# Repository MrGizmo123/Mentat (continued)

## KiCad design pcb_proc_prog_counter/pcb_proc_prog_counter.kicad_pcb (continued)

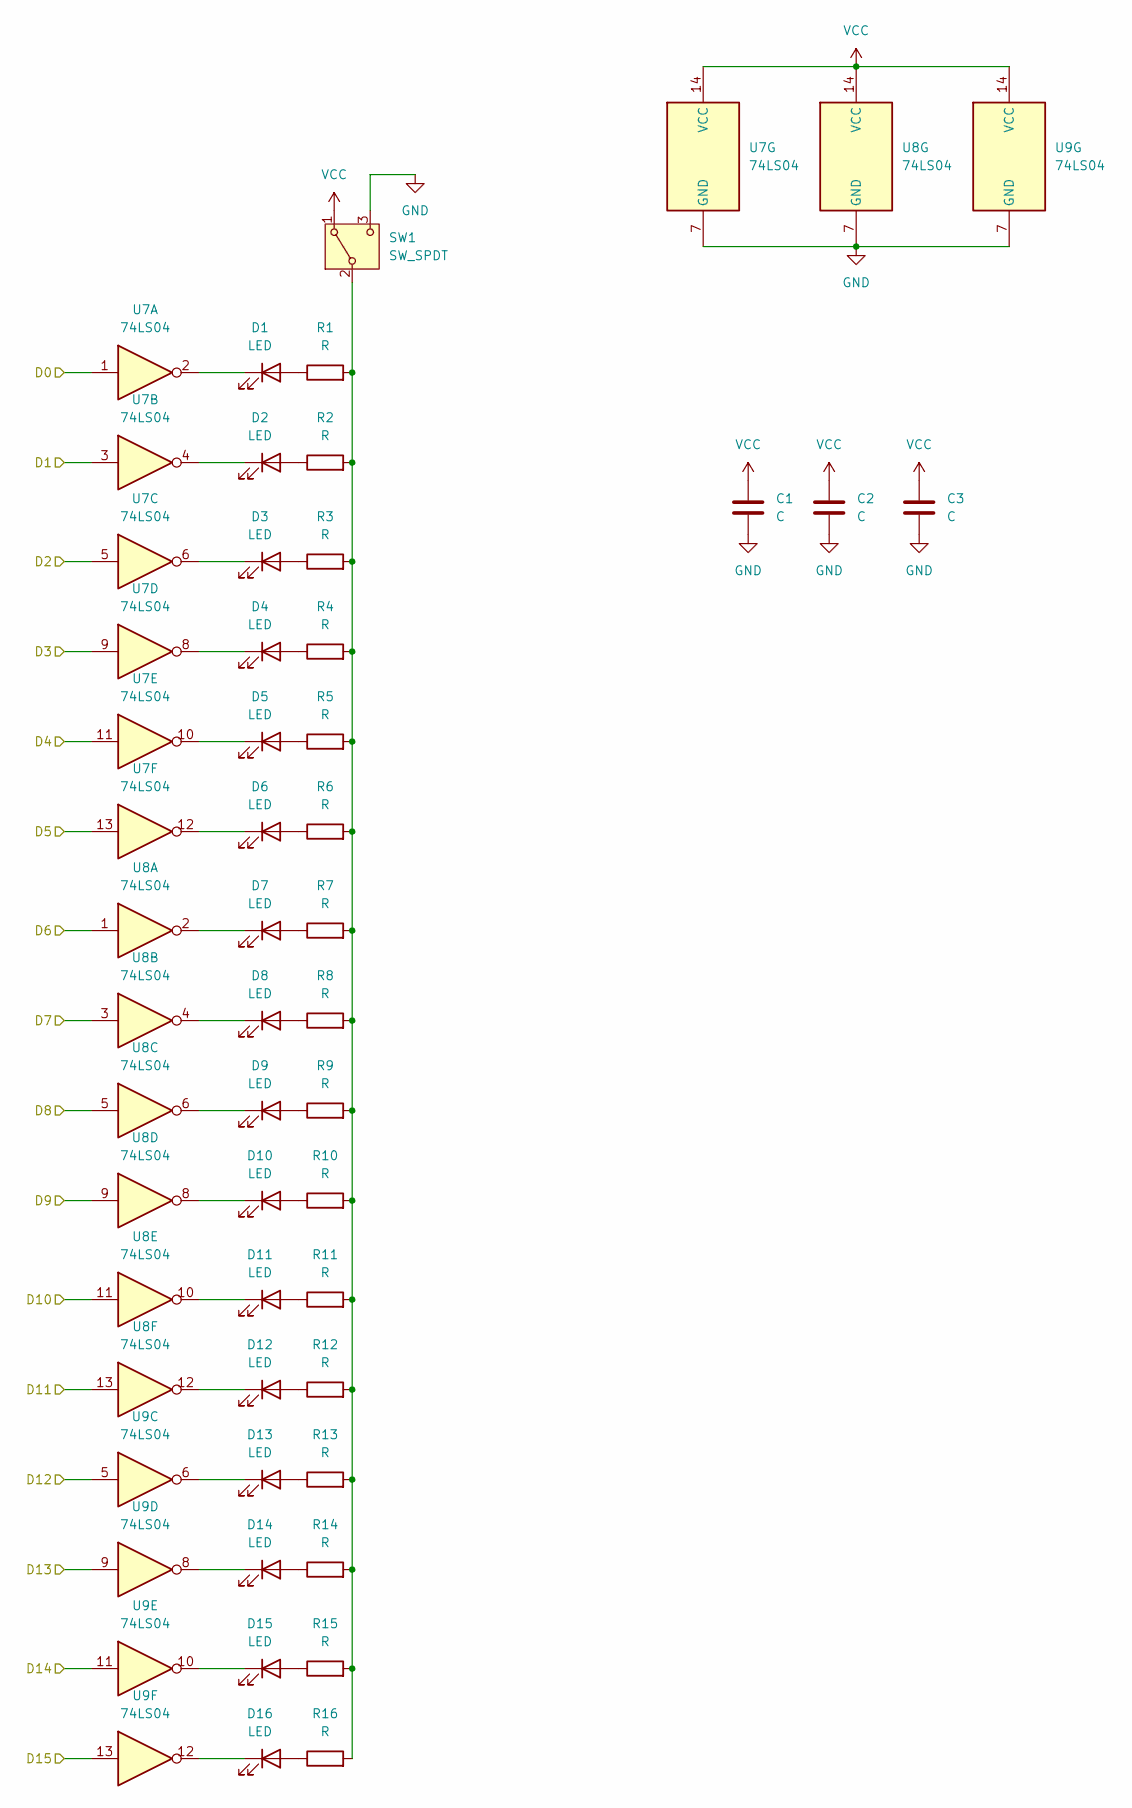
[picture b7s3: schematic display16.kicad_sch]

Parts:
C1, C2, C3: C; C_0805_2012Metric
D1, D2, D3, D4, D5, D6, D7, D8, D9, D10, D11, D12, D13, D14, D15, D16: LED; LED_Rectangular_W5.0mm_H2.0mm
R1, R2, R3, R4, R5, R6, R7, R8, R9, R10, R11, R12, R13, R14, R15, R16: R; R_0805_2012Metric
SW1: SW_SPDT; SW_E-Switch_EG1271_SPDT
U7: 74LS04; DIP-14_W7.62mm_Socket_LongPads
U8, U9: 74LS04; DIP-14_W7.62mm_LongPads

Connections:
/Display/D0: U7.1; also elsewhere on the board
/Display/D1: U7.3; also elsewhere on the board
/Display/D2: U7.5; also elsewhere on the board
/Display/D3: U7.9; also elsewhere on the board
/Display/D4: U7.11; also elsewhere on the board
/Display/D5: U7.13; also elsewhere on the board
/Display/D6: U8.1; also elsewhere on the board
/Display/D7: U8.3; also elsewhere on the board
/Display/D8: U8.5; also elsewhere on the board
/Display/D9: U8.9; also elsewhere on the board
/Display/D10: U8.11; also elsewhere on the board
/Display/D11: U8.13; also elsewhere on the board
/Display/D12: U9.5; also elsewhere on the board
/Display/D13: U9.9; also elsewhere on the board
/Display/D14: U9.11; also elsewhere on the board
/Display/D15: U9.13; also elsewhere on the board
GND: C1.2, C2.2, C3.2, SW1.3 (C), U7.7 (GND), U8.7 (GND), U9.7 (GND); also elsewhere on the board
unnamed: D1.2 (A), R1.1
unnamed: D1.1 (K), U7.2
unnamed: D2.2 (A), R2.1
unnamed: D2.1 (K), U7.4
unnamed: D3.2 (A), R3.1
unnamed: D3.1 (K), U7.6
unnamed: D4.2 (A), R4.1
unnamed: D4.1 (K), U7.8
unnamed: D5.2 (A), R5.1
unnamed: D5.1 (K), U7.10
unnamed: D6.2 (A), R6.1
unnamed: D6.1 (K), U7.12
unnamed: D7.2 (A), R7.1
unnamed: D7.1 (K), U8.2
unnamed: D8.2 (A), R8.1
unnamed: D8.1 (K), U8.4
unnamed: D9.2 (A), R9.1
unnamed: D9.1 (K), U8.6
unnamed: D10.2 (A), R10.1
unnamed: D10.1 (K), U8.8
unnamed: D11.2 (A), R11.1
unnamed: D11.1 (K), U8.10
unnamed: D12.2 (A), R12.1
unnamed: D12.1 (K), U8.12
unnamed: D13.2 (A), R13.1
unnamed: D13.1 (K), U9.6
unnamed: D14.2 (A), R14.1
unnamed: D14.1 (K), U9.8
unnamed: D15.2 (A), R15.1
unnamed: D15.1 (K), U9.10
unnamed: D16.2 (A), R16.1
unnamed: D16.1 (K), U9.12
unnamed: R1.2, R2.2, R3.2, R4.2, R5.2, R6.2, R7.2, R8.2, R9.2, R10.2, R11.2, R12.2, R13.2, R14.2, R15.2, R16.2, SW1.2 (B)
VCC: C1.1, C2.1, C3.1, SW1.1 (A), U7.14 (VCC), U8.14 (VCC), U9.14 (VCC); also elsewhere on the board

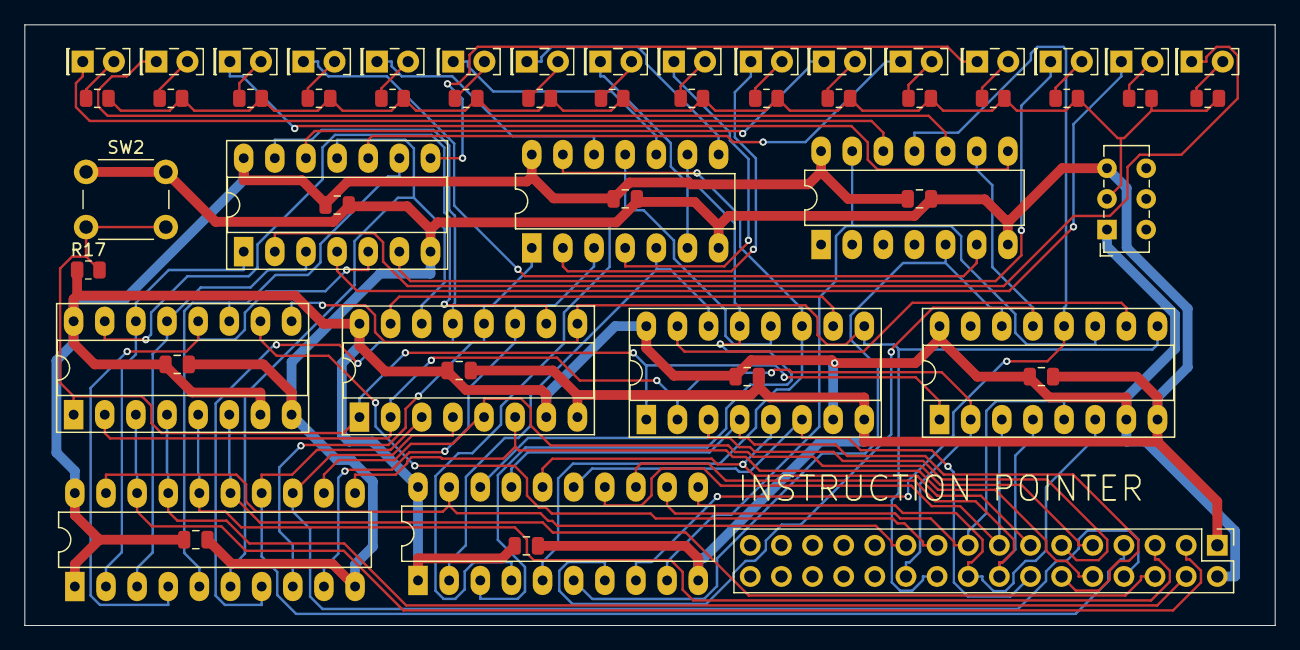
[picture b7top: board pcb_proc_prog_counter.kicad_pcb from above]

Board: 2 copper layers, 102.0 x 49.0 mm, 54 parts (0 on the bottom side), 75 nets.
